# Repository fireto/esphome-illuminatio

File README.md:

# esphome-illuminatio
Dimmable LED drivers controller based on ESP Home with HomeAssistant integration via MQTT

in order to compile and deploy this project you need to get https://esphome.io

```podman run --rm -v "${PWD}":/config --device=/dev/ttyUSB0 -it esphome/esphome ./illuminatio.yml run```

BOM

LED Drivers connector cable:
 CS-DSDMDB15MM-010

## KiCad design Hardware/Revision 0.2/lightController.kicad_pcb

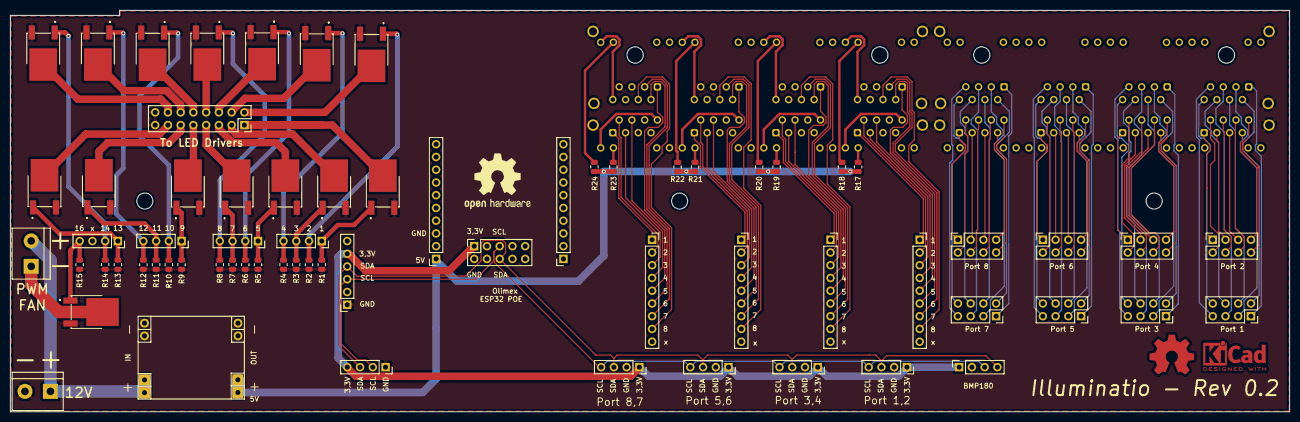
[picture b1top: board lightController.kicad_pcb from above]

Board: 2 copper layers, 255.0 x 80.0 mm, 73 parts (0 on the bottom side), 148 nets.

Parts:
H1, H2, H3: MountingHole; MountingHole_3.2mm_M3
J1, J2, J4, J5: Conn_01x04_Female; PinSocket_1x04_P2.54mm_Vertical
J3: PWD_LED_Drivers; PinSocket_2x08_P2.54mm_Vertical
J6, J19: 8P8C_LED_Shielded_x8; RJ45_Chinesium_RJX-08
J7: PCF8574_1; PinSocket_1x09_P2.54mm_Vertical
J8: PCF8574_2; PinSocket_1x09_P2.54mm_Vertical
J9: PCF8574_4; PinSocket_1x09_P2.54mm_Vertical
J10: PCF8574_3; PinSocket_1x09_P2.54mm_Vertical
J11, J14, J15, J16: Conn_01x04_PCF8574; PinSocket_1x04_P2.54mm_Vertical
J12: UEXT_Slave; PinSocket_2x05_P2.54mm_Vertical
J13: Conn_01x06_PCA9685; PinSocket_1x06_P2.54mm_Vertical
J17: Port1; PinSocket_2x04_P2.54mm_Vertical
J18: Port2; PinSocket_2x04_P2.54mm_Vertical
J20: Port3; PinSocket_2x04_P2.54mm_Vertical
J21: Port4; PinSocket_2x04_P2.54mm_Vertical
J22: Port5; PinSocket_2x04_P2.54mm_Vertical
J23: Port6; PinSocket_2x04_P2.54mm_Vertical
J24: Port7; PinSocket_2x04_P2.54mm_Vertical
J25: Port8; PinSocket_2x04_P2.54mm_Vertical
J26: esp32-PoE Left; PinSocket_1x10_P2.54mm_Vertical
J27: DC-DC step down; MP1584EN_dc-dc_module
J28: i2c_extra; PinSocket_1x04_P2.54mm_Vertical
J29: Fan PWM; TerminalBlock_bornier-2_P5.08mm
J30: Input 12V; TerminalBlock_bornier-2_P5.08mm
J31: esp32-PoE Right; PinSocket_1x10_P2.54mm_Vertical
J32: BMP180; PinSocket_1x04_P2.54mm_Vertical
Q1, Q2, Q3, Q4, Q5, Q6, Q7, Q8, Q9, Q10, Q11, Q12, Q13, Q14, Q15: FDD8447L
R1, R2, R3, R4, R5, R6, R7, R8, R9, R10, R11, R12, R13, R14, R15: 1K; R_0805_2012Metric
R17, R18, R19, R20, R21, R22, R23, R24: 150; R_0805_2012Metric

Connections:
+3V3: J11.1, J12.1, J13.5, J14.1, J15.1, J16.1, J28.4, J32.1
+5V: J26.1, J27.1, J27.2, R17.2, R18.2, R19.2, R20.2, R21.2, R22.2, R23.2, R24.2
GND: J3.15, J3.16, J6.7, J6.19, J6.31, J6.43, J6.55, J6.67, J6.79, J6.91, J6.SH, J11.2, J12.2, J13.1, J14.2, J15.2, J16.2, J19.SH, J26.3, J27.3, J27.4, J27.5, J27.6, J28.1, J30.2, J32.2, Q1.3, Q2.3, Q3.3, Q4.3, Q5.3, Q6.3, Q7.3, Q8.3, Q9.3, Q10.3, Q11.3, Q12.3, Q13.3, Q14.3, Q15.3, R1.2, R2.2, R3.2, R4.2, R5.2, R6.2, R7.2, R8.2, R9.2, R10.2, R11.2, R12.2, R13.2, R14.2, R15.2
unnamed: J3.1, Q1.2
unnamed: J3.2, Q2.2
unnamed: J3.3, Q3.2
unnamed: J3.4, Q4.2
unnamed: J3.5, Q5.2
unnamed: J3.6, Q6.2
unnamed: J3.7, Q7.2
unnamed: J3.8, Q8.2
unnamed: J3.9, Q9.2
unnamed: J3.10, Q10.2
unnamed: J3.11, Q11.2
unnamed: J3.12, Q12.2
unnamed: J3.13, Q13.2
unnamed: J3.14, Q14.2
unnamed: J6.1, J7.1
unnamed: J6.2, J7.2
unnamed: J6.3, J7.3
unnamed: J6.4, J7.4
unnamed: J6.8, J6.9
unnamed: J6.10, R17.1
unnamed: J6.13, J7.5
unnamed: J6.14, J7.6
unnamed: J6.15, J7.7
unnamed: J6.16, J7.8
unnamed: J6.20, J6.21
unnamed: J6.22, R18.1
unnamed: J6.25, J8.1
unnamed: J6.26, J8.2
unnamed: J6.27, J8.3
unnamed: J6.28, J8.4
unnamed: J6.32, J6.33
unnamed: J6.34, R19.1
unnamed: J6.37, J8.5
unnamed: J6.38, J8.6
unnamed: J6.39, J8.7
unnamed: J6.40, J8.8
unnamed: J6.44, J6.45
unnamed: J6.46, R20.1
unnamed: J6.56, J6.57
unnamed: J6.58, R21.1
unnamed: J6.68, J6.69
unnamed: J6.70, R22.1
unnamed: J6.73, J9.1
unnamed: J6.74, J9.2
unnamed: J6.75, J9.3
unnamed: J6.76, J9.4
unnamed: J6.80, J6.81
unnamed: J6.82, R23.1
unnamed: J6.85, J9.5
unnamed: J6.86, J9.6
unnamed: J6.87, J9.7
unnamed: J6.88, J9.8
unnamed: J6.92, J6.93
unnamed: J6.94, R24.1
unnamed: J6.49, J10.1
unnamed: J6.50, J10.2
unnamed: J6.51, J10.3
unnamed: J6.52, J10.4
unnamed: J6.61, J10.5
unnamed: J6.62, J10.6
unnamed: J6.63, J10.7
unnamed: J6.64, J10.8
unnamed: J17.1, J19.1
unnamed: J17.2, J19.2
unnamed: J17.3, J19.3
unnamed: J17.4, J19.4
unnamed: J17.5, J19.5
unnamed: J17.6, J19.6
unnamed: J17.7, J19.7
unnamed: J17.8, J19.8
unnamed: J18.1, J19.13
unnamed: J18.2, J19.14
unnamed: J18.3, J19.15
unnamed: J18.4, J19.16
unnamed: J18.5, J19.17
unnamed: J18.6, J19.18
unnamed: J18.7, J19.19
unnamed: J18.8, J19.20
unnamed: J19.25, J20.1
unnamed: J19.26, J20.2
unnamed: J19.27, J20.3
unnamed: J19.28, J20.4
unnamed: J19.29, J20.5
unnamed: J19.30, J20.6
unnamed: J19.31, J20.7
unnamed: J19.32, J20.8
unnamed: J19.37, J21.1
unnamed: J19.38, J21.2
unnamed: J19.39, J21.3
unnamed: J19.40, J21.4
unnamed: J19.41, J21.5
unnamed: J19.42, J21.6
unnamed: J19.43, J21.7
unnamed: J19.44, J21.8
unnamed: J19.49, J22.1
unnamed: J19.50, J22.2
unnamed: J19.51, J22.3
unnamed: J19.52, J22.4
unnamed: J19.53, J22.5
unnamed: J19.54, J22.6
unnamed: J19.55, J22.7
unnamed: J19.56, J22.8
unnamed: J19.61, J23.1
unnamed: J19.62, J23.2
unnamed: J19.63, J23.3
unnamed: J19.64, J23.4
unnamed: J19.65, J23.5
unnamed: J19.66, J23.6
unnamed: J19.67, J23.7
unnamed: J19.68, J23.8
unnamed: J19.73, J24.1
unnamed: J19.74, J24.2
unnamed: J19.75, J24.3
unnamed: J19.76, J24.4
unnamed: J19.77, J24.5
unnamed: J19.78, J24.6
unnamed: J19.79, J24.7
unnamed: J19.80, J24.8
unnamed: J19.85, J25.1
unnamed: J19.86, J25.2
unnamed: J19.87, J25.3
unnamed: J19.88, J25.4
unnamed: J19.89, J25.5
unnamed: J19.90, J25.6
unnamed: J19.91, J25.7
unnamed: J19.92, J25.8
unnamed: J29.1, Q15.2
PWM01: J4.1, Q1.1, R1.1
PWM02: J4.2, Q2.1, R2.1
PWM03: J4.3, Q3.1, R3.1
PWM04: J4.4, Q4.1, R4.1
PWM05: J5.1, Q5.1, R5.1
PWM06: J5.2, Q6.1, R6.1
PWM07: J5.3, Q7.1, R7.1
PWM08: J5.4, Q8.1, R8.1
PWM09: J1.1, Q9.1, R9.1
PWM10: J1.2, Q10.1, R10.1
PWM11: J1.3, Q11.1, R11.1
PWM12: J1.4, Q12.1, R12.1
PWM13: J2.1, Q13.1, R13.1
PWM14: J2.2, Q14.1, R14.1
PWM16: J2.4, Q15.1, R15.1
SCL: J11.4, J12.5, J13.3, J14.4, J15.4, J16.4, J28.2, J32.3
SDA: J11.3, J12.6, J13.4, J14.3, J15.3, J16.3, J28.3, J32.4
VCC: J27.7, J27.8, J29.2, J30.1

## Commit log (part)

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2021-03-19 Initial structure + ealry settings for hallwaySwitch
2021-03-28 Adding hardware KiCad project
2021-03-28 Adding functionality to limit min PWM, as driver does start at PWD < 40%
2021-03-31 Adding BMP180 temperature sensor inside the enclosure
2021-07-25 Updating switch_mapping.ods
2021-07-25 separate configs for first and second floor controllers
2021-08-17 update I/O mapping
2021-08-17 fialize switch behaviour for floor 1
2021-10-23 floor1 rc1 , switch logging Verbose -> Debug
2021-10-23 adding webserver common config file
2021-10-23 moving switch - light mapping to external file: fl1SwitchMapping.yml
2021-10-24 floor2 rc1
2021-10-30 renaming all switches and lights on floor2 to have fl2 prefix
2021-10-30 renaming all switches and lights on floor1 to have fl1 prefix. Adding max dimming value.
2022-09-29 new version of kcad files
2022-09-29 remap keys: remove fl1BathroomShower, individual control living room ceiling 3 drivers
2022-09-29 remove reboot if mqtt not connected
2022-09-29 FL1: disable API, configrure min-max dimming in Output, add UptimeHumanReadable, remove transition time for switches, apply rempapped rules, cahnge min-max dimming as now we use 100% of the range
2022-10-17 FL2: disable API, configrure min-max dimming in Output, add UptimeHumanReadable, remove transition time for switches, apply rempapped rules, cahnge min-max dimming as now we use 100% of the range
2023-07-21 Enable EspHome API, rename devices
2023-07-26 dissable mqtt
2023-08-24 remove uptime human readable, add restore_mode
2023-09-19 Add relay output for fron door lock, reconfigure relay outputs as binary light
2025-03-07 Enable OTA updates with ESPHome platform, update web server version, and refactor ESP32 platform declaration in configuration files
2026-06-11 Convert water heater and front door lock to output switches, rename floor heating to water heater, fix deprecated ethernet clk_mode
